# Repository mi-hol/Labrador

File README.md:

# What is it?
The [EspoTek Labrador](http://espotek.com/labrador) is an open-source board that turns your PC, Raspberry Pi, or Android Smartphone into a full-featured electronics lab bench, complete with oscilloscope, signal generator, and more.

This repo hosts all of the software and hardware that makes Labrador possible.

# Tutorial
If you're new to Labrador or oscilloscopes in general, I strongly recommend checking out the fantastic [tutorial series](https://www.wellys.com/posts/courses_electronics/) produced by Lief Koepsel.  It features well-written, rich articles as well as video content that explains everything more clearly than I ever could!

# Getting Started
Binary (executable) versions of the software are available for [download](https://github.com/espotek-org/Labrador/releases) for several platforms.

For the documentation, please visit the [wiki](https://github.com/espotek-org/Labrador/wiki).

## Building from Source
If you're looking to build from source but don't know where to start, Qt Creator is the easiest way to get your toes wet!  
https://www.qt.io/download-open-source/  
When installing, make sure you tick the box to install Qt 5.15 or later.

Once it's installed, open `Desktop_Interface/Labrador.pro`, then Clean All -> Run `qmake` -> Build All.

If you're on Linux (including Raspberry Pi), then you can also build the software from source by cloning the repo, `cd`ing to the `Desktop_Interface` directory, then running:  
```
QT_SELECT=qt5 qmake
make
sudo make install
sudo ldconfig
```
Then, to launch, just type `labrador` into the terminal.  Additional packages may be required, please see the full [build instructions](https://github.com/espotek-org/Labrador/wiki/Building-from-source) on the wiki.

On macOS, additional steps may be required.  See issue https://github.com/espotek-org/Labrador/issues/238

To build the AVR software, I use Atmel Studio 7.  Just load up the .atsln and push F7.  You can use `avr-gcc` if you don't want to install a full IDE.

The PCB files can be edited in KiCAD 5.0 or later.

# Extras
There are community contributed 3D printable cases available at Thingiverse, courtesy of SpaceBex and Bostwickenator:
* https://www.thingiverse.com/thing:3188243
* https://www.thingiverse.com/thing:4705392

Dave Messink has designed [a case that can be laser cut from 3mm plywood](https://github.com/espotek-org/Labrador/files/13813693/Re__Labrador_Case.1.zip).  The [binding posts](https://www.amazon.com/dp/B07YKYP8MN) and [cables](https://www.amazon.com/dp/B08KZGPTLM) he used are from Amazon.  

# Licence
All Desktop software files are licenced under [GNU GPL v3](https://www.gnu.org/licenses/gpl.html).

All Microcontroller software files, with the exception of those provided by Atmel, are licenced under the [3-Clause BSD License](https://opensource.org/licenses/BSD-3-Clause).

All hardware files (schematics, PCB) are licenced under [Creative Commons 4.0 (CC BY-NC-SA)](https://creativecommons.org/licenses/by-nc-sa/4.0/).

# Collaboration
If you want to submit a Pull Request, bug report, or feature request, please feel free to do so here at GitHub.  
If you just want to say hello and remind me that people are actually using my product, please email admin@espotek.com

Thanks to all.  
~Chris

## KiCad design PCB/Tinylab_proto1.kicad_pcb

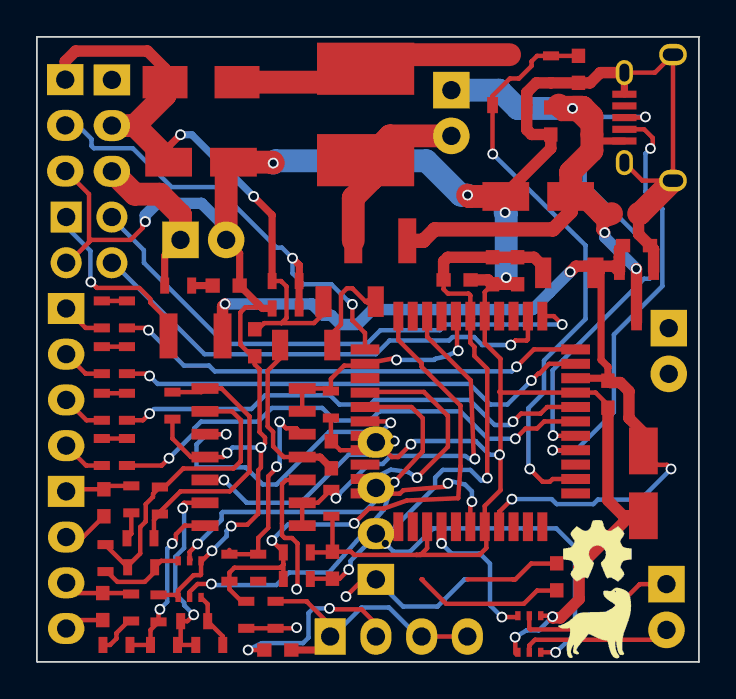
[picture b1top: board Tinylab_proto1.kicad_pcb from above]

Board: 2 copper layers, 36.8 x 34.7 mm, 76 parts (0 on the bottom side), 59 nets.

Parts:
C1, C2, C7, C8, C10, C11, C12, C13, C14, C16, C17, C18: C; C_0603
C3, C4, C5: C_Small; C_0603
C6, C9, C15: CP1; c_elec_4x5.3
D1: D_Schottky; SMA_Standard
D2: LED; LED_0603
F1, F2: F_Small; C_1210
IC1: ATXMEGA32A4U-AU; LQFP-44_10x10mm_Pitch0.8mm
L1: INDUCTOR; SMALL_INDUCTOR
L2, L3, L4: INDUCTOR; R_1206
Main_Logo: LARGE_LOGO; logo175dpi
P1, P5: SCOPE_OUT; Pin_Header_Straight_1x04
P2: USB_OTG; USB_Micro-B_WIDE
P3: DIG_OUT; Pin_Header_Straight_1x04
P4: PDI/3V3; Pin_Header_Straight_2x02
P6: DAC_OUT; Pin_Header_Straight_1x04
P7: PSU; Pin_Header_Straight_1x02
P8: DIG_IN; Pin_Header_Straight_1x02
P9: FUSE_BYPASS; Pin_Header_Straight_1x02
P10: EXPANSION; Pin_Header_Straight_1x03
P11: SWITCH; Pin_Header_Straight_1x03
Q1: Q_NMOS_GSD; SOT-23-3
R1, R2: 1M; R_0603
R3, R4: 75K; R_0603
R5, R6, R15, R16, R17, R18, R19, R20, R21, R26, R28, R29, R30, R31, R32: 1K; R_0603
R7, R8, R9, R10, R11, R12, R13, R14, R22, R23, R24, R25: 28R; R_0603
R27: 100R; R_0603
U1: 78L05; SOT-23-3
U2: LM324; SOIC-14_3.9x8.7mm_Pitch1.27mm
U3, U4: DMN63D8LDW; SOT-363

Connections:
+5V: C3.1, C9.1, C10.1, F2.1, P2.1, P9.1, U1.3
/3V3_OUT: F1.1, P4.1
/AVCC: C5.1, C8.1, C17.1, C18.1, IC1.39, L2.2, R5.1
/AVCC_ON_2: IC1.44, R3.2, R4.1, R5.2, R6.2
/Buffered_DAC_CH1: R19.1, R22.2, R29.1, U2.8
/Buffered_DAC_CH2: R20.1, R23.2, R30.2, U2.14
/CH1: IC1.42, R21.1, U2.1, U2.2
/CH2: IC1.2, IC1.40, R28.2, U2.6, U2.7
/D0-prefuse: IC1.28, R11.1
/D0_MID: R7.1, R11.2
/D0_OUT: P3.4, R7.2
/D1-prefuse: IC1.29, R12.1
/D1_MID: R8.1, R12.2
/D1_OUT: P3.3, R8.2
/D2-OUT: P3.2, R9.2
/D2-prefuse: IC1.32, R13.1
/D2_MID: R9.1, R13.2
/D3-OUT: P3.1, R10.2
/D3-prefuse: IC1.33, R14.1
/D3_MID: R10.1, R14.2
/D+: IC1.27, P2.3
/D-: IC1.26, P2.2
/DAC_OUT: IC1.6, U2.10
/DAC_OUT2: IC1.7, U2.12
/DIG_CH1: IC1.15, U4.6
/DIG_CH2: IC1.12, U4.3
/L-Ana_IN_CH1: P8.1, U4.5
/L-Ana_IN_CH2: P8.2, U4.2
/OPAMP_VCC: C16.1, L4.1, U2.4
/PDI_CLK: IC1.34, P4.2
/PDI_DATA: IC1.35, P4.4
/PSU_FDBK: IC1.1, P10.2, R26.2, R27.1
/PSU_OUT: P7.1, P11.3, R32.1
/PSU_PWM: C12.1, IC1.24, Q1.1, R31.1
/PSU_Unfiltered_Raw: C7.1, C15.1, D1.1, L3.2, P10.1, P11.2, R26.1
/QTop: D1.2, L1.1, Q1.3
/R22-R24: R22.1, R24.2
/R23-R25: R23.1, R25.2
/S-Gen_CH1_AC: C13.1, P6.2
/S-Gen_CH1_DC: C13.2, P6.1, R24.1
/S-Gen_CH2_AC: C14.1, P6.4
/S-Gen_CH2_DC: C14.2, P6.3, R25.1
/S-Gen_Drain_Top_CH1: R17.2, R18.2, U3.3
/S-Gen_Drain_Top_CH2: R15.2, R16.2, U3.6
/Scoe_CH1_AC: C1.2, P1.2
/Scope_Buffer_Input_CH2: R1.1, R2.1, R3.1, R4.2, U2.5
/Scope_CH1_DC: C1.1, P1.1, P1.3, P1.4, R2.2
/Scope_CH2_AC: C2.2, P5.2
/Scope_CH2_DC: C2.1, P5.1, P5.3, P5.4, R1.2
/TO_B0: IC1.4, U3.2
/TO_B1: IC1.5, U3.5
/VCC_3V3: C4.1, C6.1, C11.1, F1.2, IC1.19, IC1.31, L2.1, U1.2
/VGND: C3.2, C4.2, C5.2, C6.2, C7.2, C8.2, C9.2, C10.2, C11.2, C12.2, C15.2, C16.2, C17.2, C18.2, D2.1, IC1.8, IC1.14, IC1.18, IC1.30, IC1.38, P2.5, P2.6, P4.3, P7.2, P10.3, Q1.2, R6.1, R21.2, R27.2, R28.1, R29.2, R30.1, R31.2, U1.1, U2.11, U3.1, U3.4, U4.1, U4.4
/V_minus_dac_out: R17.1, R18.1, R19.2, U2.9
/V_minus_dac_out2: R15.1, R16.1, R20.2, U2.13
/XCK: IC1.11, IC1.17
unnamed: D2.2, R32.2
unnamed: F2.2, L1.2, P9.2
unnamed: L3.1, L4.2

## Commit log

2025-06-28 Pseudo Random Binary Sequence (PRBS-5) waveform generator
2025-06-28 eye diagram UI
2025-06-28 eye diagram calculation
2025-07-04 Updated issue template
2025-07-06 missing DISABLE_SPECTRUM preprocessor directive
2025-07-28 add arm64-v8a USBlib
2025-07-28 Revert "add arm64-v8a USBlib"
    This reverts commit acfbd678671e59c8bb204d4324b476e45c678b8e.
2025-08-22 Correct typo
2025-09-05 Update Windows workflow to use Windows 2022 (#350)
    * Update Windows workflow to use Windows 2022
    * Changed toolset to 14.2
    ---------
2025-09-05 added zoom feature to spectrum analyzer and frequency response tools
2025-09-09 removed commented code lines
2025-09-09 removed more comments
2025-09-09 reverted PCB to genuine version
2025-09-09 removed unused var
2025-09-10 Zoom feature for the spectrum analyzer and frequency response tools (#352)
    * added zoom feature to spectrum analyzer and frequency response tools
    * removed commented code lines
    * removed more comments
    * reverted PCB to genuine version
    * removed unused var
2025-09-18 added DISABLE_SPECTRUM guards to DisplayControl:setRespAndSpecRanges
2025-09-27 fixed minor time ticking bug (#357)
    * fixed minor time ticking bug
    * avoiding some hard-coded ticking settings
    * reverted PCB changes to genuine version again; deleted debug statements in isodriver.cpp
2025-09-30 Update macos to version 15 becasue 13 is now unsupported
    for details see https://github.com/espotek-org/Labrador/pull/357#issuecomment-3344215671
2025-10-07 fix default branch name
2025-10-10 Code Signing on macos
2025-10-12 Build uses macos-15-intel
2025-10-12 Potential fix for code scanning alert no. 10: Workflow does not contain permissions
2025-10-12 Potential fix for code scanning alert no. 10: Workflow does not contain permissions (#2)
2025-10-12 Potential fix for code scanning alert no. 8: Workflow does not contain permissions
2025-10-12 Potential fix for code scanning alert no. 8: Workflow does not contain permissions (#3)
    * Potential fix for code scanning alert no. 10: Workflow does not contain permissions
    * Potential fix for code scanning alert no. 8: Workflow does not contain permissions
    ---------
2025-10-12 Potential fix for code scanning alert no. 4: Workflow does not contain permissions
2025-11-01 Add permissions to Windows build workflow
2025-11-01 Update permissions in macOS workflow
2025-11-01 Add permissions section to macOS workflow
2025-11-01 Update permissions in Linux workflow
    Added permissions for content and pull requests.
2025-11-01 Add permissions to continuous release workflow
2025-11-01 Update Android workflow permissions
    Add permissions for contents and pull-requests.
2025-11-03 Update continuous.yml (no longer marked as prerelease)
2025-11-09 added Makefile for firmware
2025-11-09 added link to wiki in the Makefile
2025-12-09 arm64-v8a build (#370)
    Thanks, Brent!
2025-12-09 hopefully resolved bug
2025-12-09 PendingIntent.FLAG_MUTABLE on Bootloader too
2025-12-09 incremented ANDROID_VERSION_CODE for Google Play publishing
2025-12-09 Also did ANDROID_VERSION_NAME
2025-12-13 brute forcing qmessagebox management and enabling calibration initiation on Android when connected to the board before UI startup
2025-12-13 removed unsigned apk
2025-12-15 added comment
2025-12-17 Add push and pull_request triggers to Windows workflow
2026-01-27 Comment out excessive logging in control transfer
    Comment out logging of bytes transferred to reduce log pollution.
